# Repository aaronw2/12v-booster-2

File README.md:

# 12v-booster-2
Second generation 5V to 12V booster

My first generation booster was severely limited in the amount of current it could produce. This second generation is designed to handle 2A.

J2 is the input with the following pin designations:
1: +5V
2: +5V
3: GND
4: GND
5: GND
6: PWM_CTL - this drives the PWM mosfet gate with a 100K pull-down

J1 is the output with the following pin designations:
1: +12V
2: +12V
3: GND
4: GND
5: GND
6: PWM output pulled to ground when PWM_CTL is high

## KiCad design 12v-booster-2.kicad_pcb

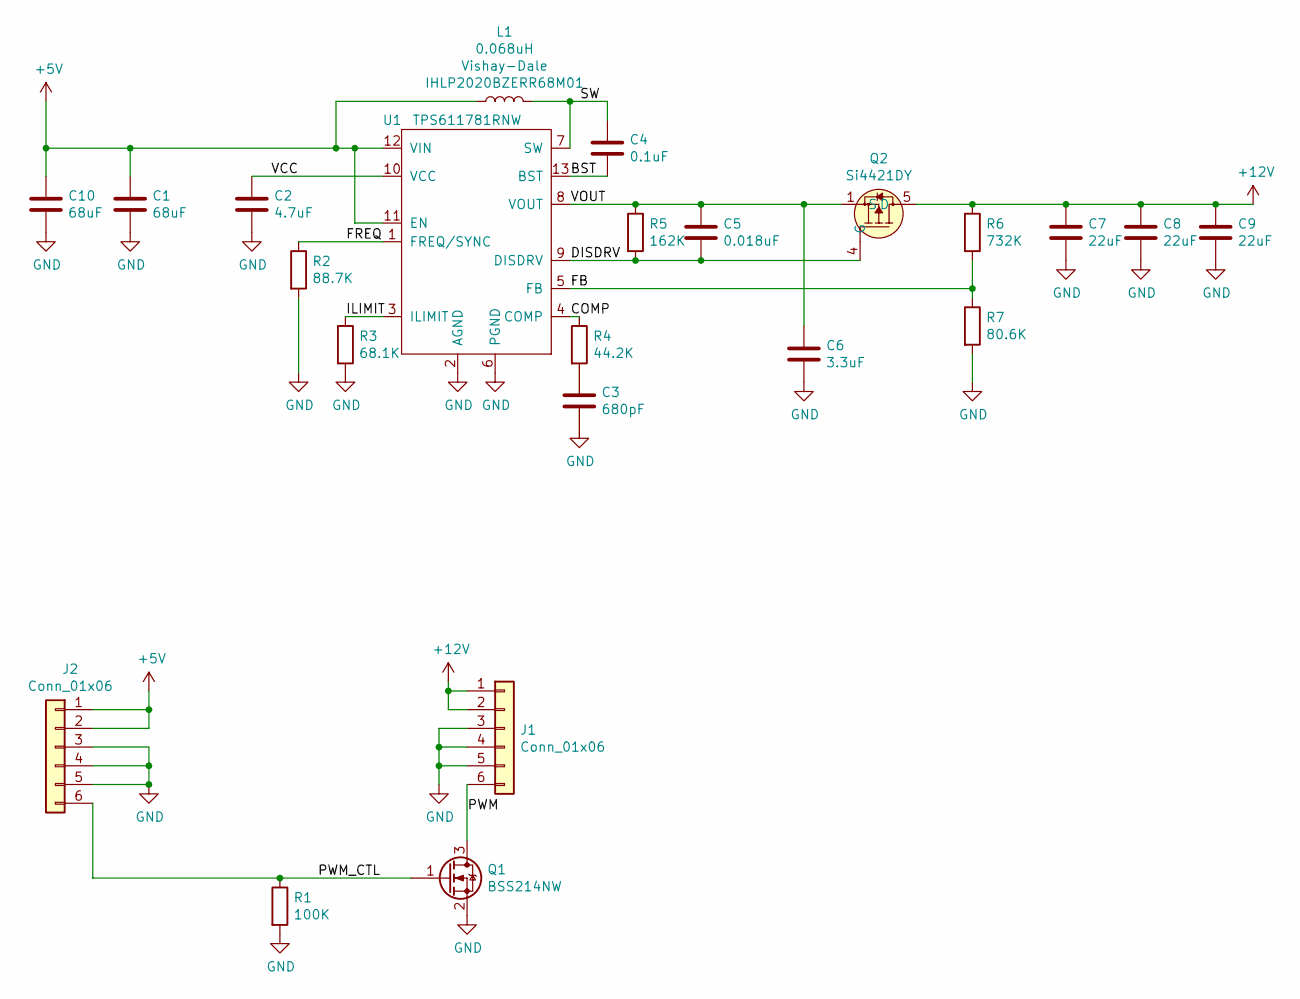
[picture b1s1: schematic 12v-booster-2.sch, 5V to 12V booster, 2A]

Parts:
C1, C10: 68uF; C_1206_3216Metric; MPN C3216X5R1A686M160AC
C2: 4.7uF; C_0603_1608Metric; MPN C1608X5R1E475K080AC
C3: 680pF; C_0603_1608Metric; MPN 885012206107
C4: 0.1uF; C_0603_1608Metric; MPN CL10B104KO8WPNC
C5: 0.018uF; C_0603_1608Metric; MPN C0603C183J3RAC7867
C6: 3.3uF; C_0603_1608Metric; MPN C1608X5R1V335K080AC
C7, C8, C9: 22uF; C_0805_2012Metric; MPN C2012X5R1V226M125AC
J1, J2: Conn_01x06; PinHeader_1x06_P2.54mm_Vertical
L1: 0.068uH; L_Vishay_IHLP-2020; MPN IHLP2020BZERR68M01
Q1: BSS214NW; SOT-323_SC-70; MPN BSS214NWH6327XTSA1
Q2: Si4421DY; SOIC127P600X175-8N; MPN SI4421DY-T1-E3
R1: 100K; R_0603_1608Metric; MPN RC0603JR-07100KL
R2: 88.7K; R_0603_1608Metric; MPN RC0603FR-0788K7L
R3: 68.1K; R_0603_1608Metric; MPN RC0603FR-0768K1L
R4: 44.2K; R_0603_1608Metric; MPN RC0603FR-0744K2L
R5: 162K; R_0603_1608Metric; MPN TNPW0603162KBEEA
R6: 732K; R_0603_1608Metric; MPN RC0603FR-07732KL
R7: 80.6K; R_0603_1608Metric; MPN CRCW060380K6FKEA
U1: TPS611781RNW; Texas_13_3.0x3.5mm_VQFN_Hotrod_Pitch_0.5mm; MPN TPS611781RNWR

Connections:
+5V: C1.1, C10.1, J2.1, J2.2, L1.1, U1.11 (EN), U1.12 (VIN)
+12V: C7.1, C8.1, C9.1, J1.1, J1.2, Q2.5 (D), Q2.6 (D), Q2.7 (D), Q2.8 (D), R6.1
/BST: C4.2, U1.13 (BST)
/COMP: R4.1, U1.4 (COMP)
/DISDRV: C5.2, Q2.4 (G), R5.2, U1.9 (DISDRV)
/FB: R6.2, R7.1, U1.5 (FB)
/FREQ: R2.1, U1.1 (FREQ/SYNC)
/ILIMIT: R3.1, U1.3 (ILIMIT)
/PWM: J1.6, Q1.3 (D)
/PWM_CTL: J2.6, Q1.1 (G), R1.1
/SW: C4.1, L1.2, U1.7 (SW)
/VCC: C2.1, U1.10 (VCC)
/VOUT: C5.1, C6.1, Q2.1 (S), Q2.2 (S), Q2.3 (S), R5.1, U1.8 (VOUT)
GND: C1.2, C2.2, C3.2, C6.2, C7.2, C8.2, C9.2, C10.2, J1.3, J1.4, J1.5, J2.3, J2.4, J2.5, Q1.2 (S), R1.2, R2.2, R3.2, R7.2, U1.2 (AGND), U1.6 (PGND)
unnamed: C3.1, R4.2

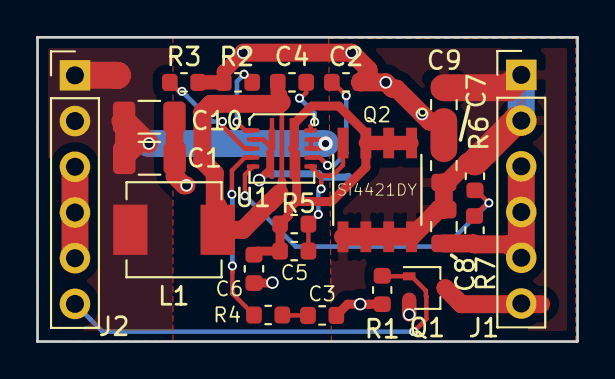
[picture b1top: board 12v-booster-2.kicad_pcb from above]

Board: 2 copper layers, 30.0 x 16.9 mm, 23 parts (0 on the bottom side), 15 nets.

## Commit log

2018-10-31 Updated README
    Prepare for initial check-in of 1.0
2018-10-31 Initial checkin of version 1.0
2018-10-31 Added missing BOM
2018-10-31 Increased output to 2A
2018-10-31 Updated to rev 1.1
2018-10-31 Fixed BOM for v1.1.

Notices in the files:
12v-booster-2.kicad_pcb:
Copyright © 2018 by Aaron Williams
